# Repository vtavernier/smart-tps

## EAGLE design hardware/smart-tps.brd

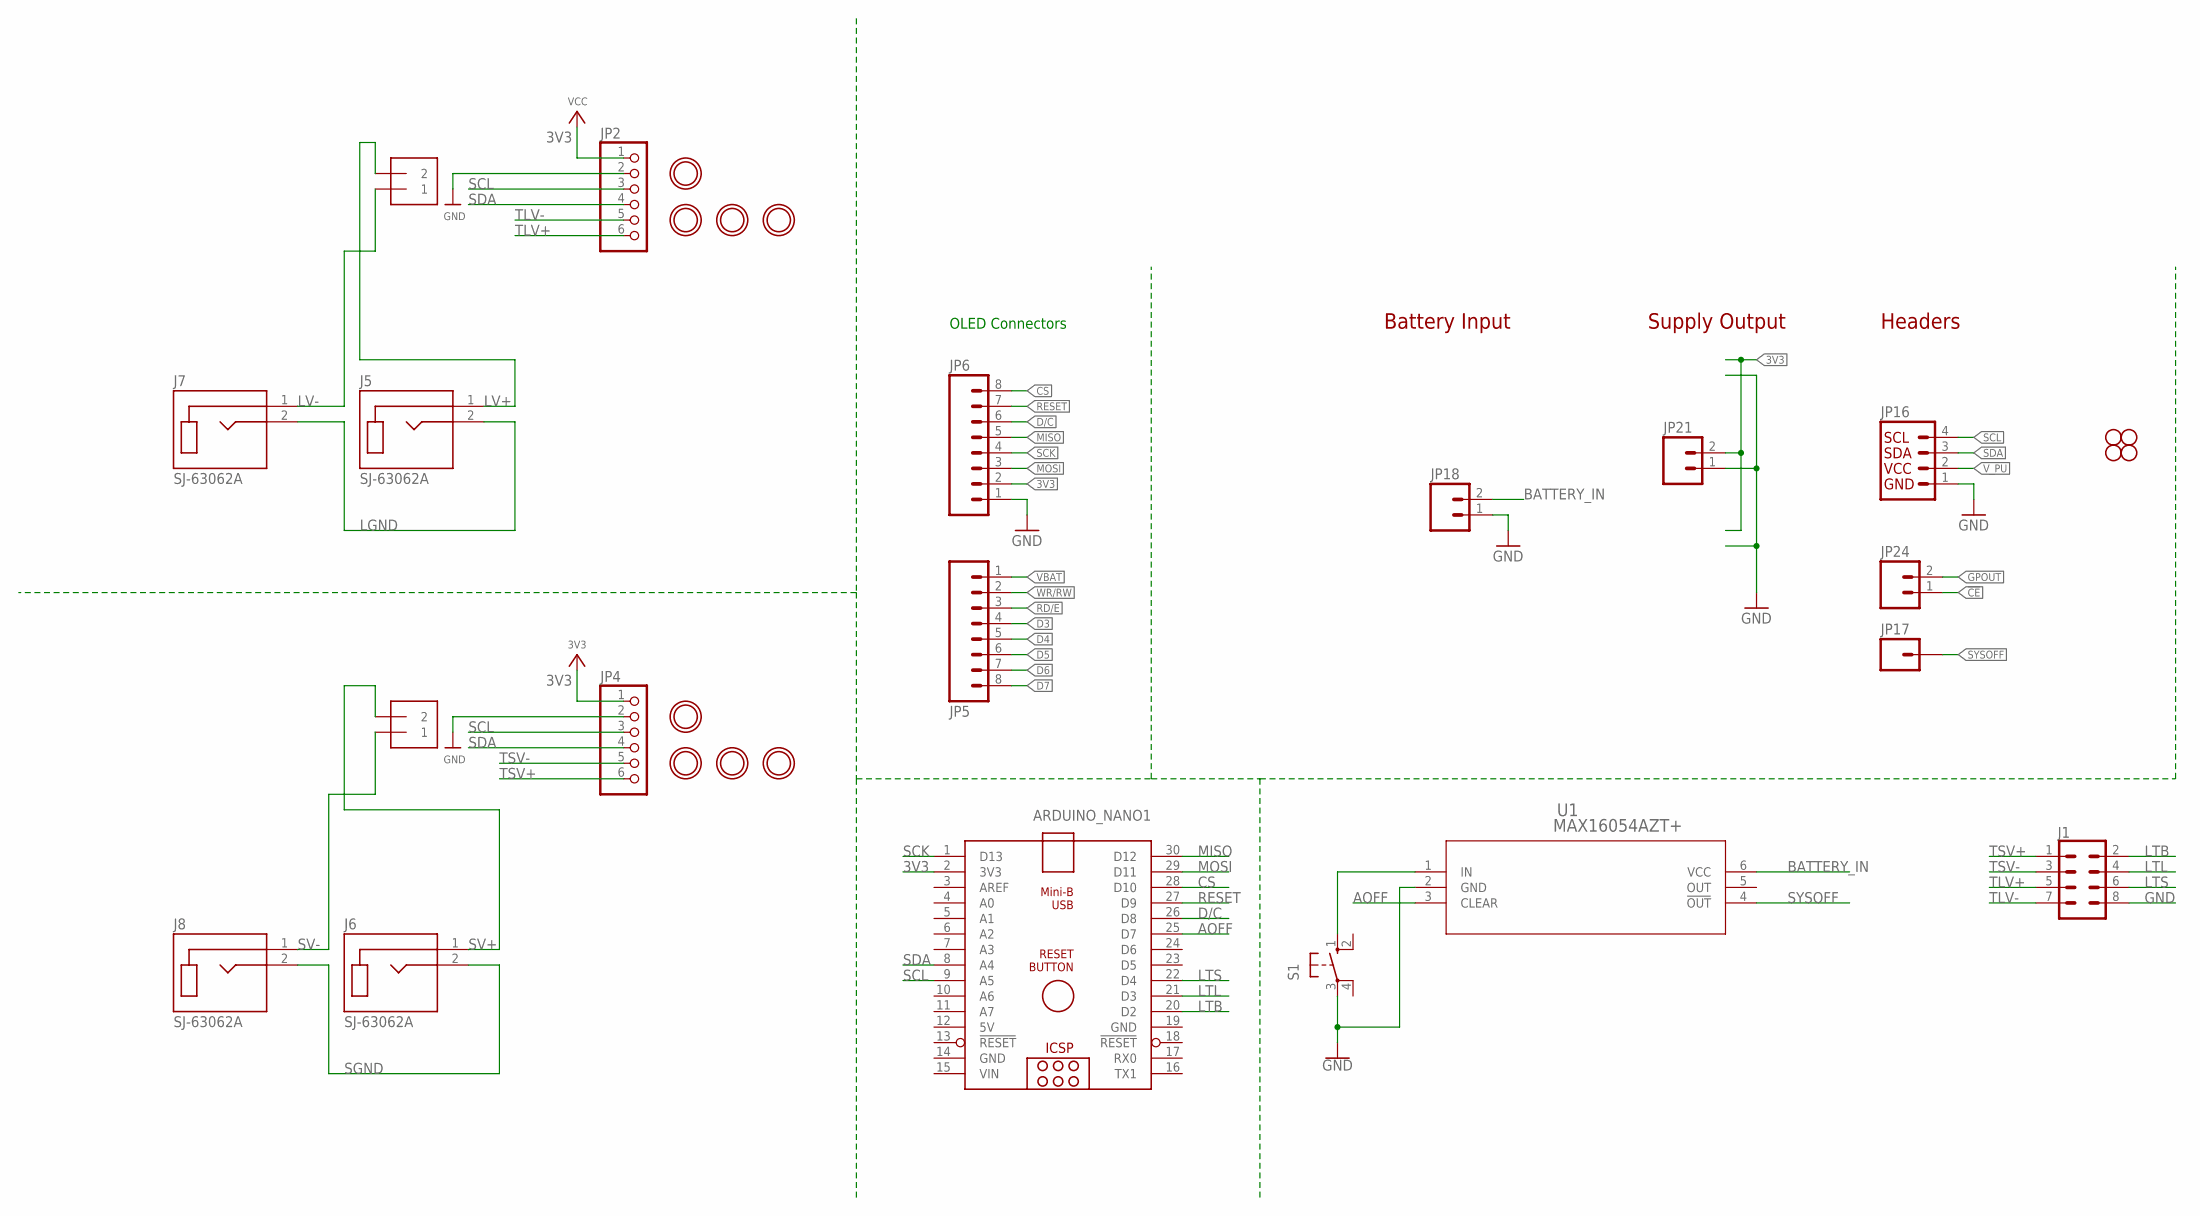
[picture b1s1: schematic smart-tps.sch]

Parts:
ARDUINO_NANO1: ARDUINO_NANO
J1: CONN_04X2; 2X4
J2, J4: TERMBLOCK_1X2-3.5MM; 1X2-3.5MM
J5, J6, J7, J8: SJ-63062A; CUI_SJ-63062A
JP2, JP4: HEADER-1X670MIL; 1X06_ROUND_70
JP5, JP6: M08; 1X08_PIN1_NO_SILK
JP16: I2C_STANDARD_NO_SILK; 1X04_NO_SILK
JP17: M01PTH_NO_SILK_YES_STOP; 1X01_NO_SILK
JP18, JP21, JP24: M021X02_NO_SILK; 1X02_NO_SILK@1
S1: 10-XX; B3F-10XX
STANDOFF5, STANDOFF6, STANDOFF7, STANDOFF8: STAND-OFF
U1: MAX16054AZT+; 21-0114C_MXM
U$18, U$19, U$20, U$21, U$40, U$41, U$42, U$43: MOUNTINGHOLE2.5; MOUNTINGHOLE_2.5_PLATED

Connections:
3V3: ARDUINO_NANO1.2 (3V3), JP2.1, JP4.1, JP6.2, JP21.2
5V: ARDUINO_NANO1.12 (5V)
!CE!: JP24.1
AOFF: ARDUINO_NANO1.25 (D7), U1.3 (CLEAR)
BATTERY_IN: JP18.2, U1.6 (VCC)
CS: ARDUINO_NANO1.28 (D10), JP6.8
D3: JP5.4
D4: JP5.5
D5: JP5.6
D6: JP5.7
D7: JP5.8
D/C: ARDUINO_NANO1.26 (D8), JP6.6
GND: ARDUINO_NANO1.14 (GND), ARDUINO_NANO1.19 (GND), J1.8, JP2.2, JP4.2, JP6.1, JP16.1, JP18.1, JP21.1, S1.3, U1.2 (GND)
GPOUT: JP24.2
LGND: J5.2 (TIP), J7.2 (TIP)
LTB: ARDUINO_NANO1.20 (D2), J1.2
LTL: ARDUINO_NANO1.21 (D3), J1.4
LTS: ARDUINO_NANO1.22 (D4), J1.6
LV+: J2.2, J5.1 (SLEEVE)
LV-: J2.1, J7.1 (SLEEVE)
MISO: ARDUINO_NANO1.30 (D12), JP6.5
MOSI: ARDUINO_NANO1.29 (D11), JP6.3
unnamed: S1.1 (S), U1.1 (IN)
RD/E: JP5.3
RESET: ARDUINO_NANO1.27 (D9), JP6.7
SCK: ARDUINO_NANO1.1 (D13), JP6.4
SCL: ARDUINO_NANO1.9 (A5), JP2.3, JP4.3, JP16.4
SDA: ARDUINO_NANO1.8 (A4), JP2.4, JP4.4, JP16.3
SGND: J6.2 (TIP), J8.2 (TIP)
SV+: J4.2, J6.1 (SLEEVE)
SV-: J4.1, J8.1 (SLEEVE)
SYSOFF: JP17.1, U1.4 (!OUT)
TLV+: J1.5, JP2.6
TLV-: J1.7, JP2.5
TSV+: J1.1, JP4.6
TSV-: J1.3, JP4.5
VBAT: JP5.1
VIN: ARDUINO_NANO1.15 (VIN)
V_PU: JP16.2
WR/RW: JP5.2

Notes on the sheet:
Battery Input
Supply Output
Headers
OLED Connectors

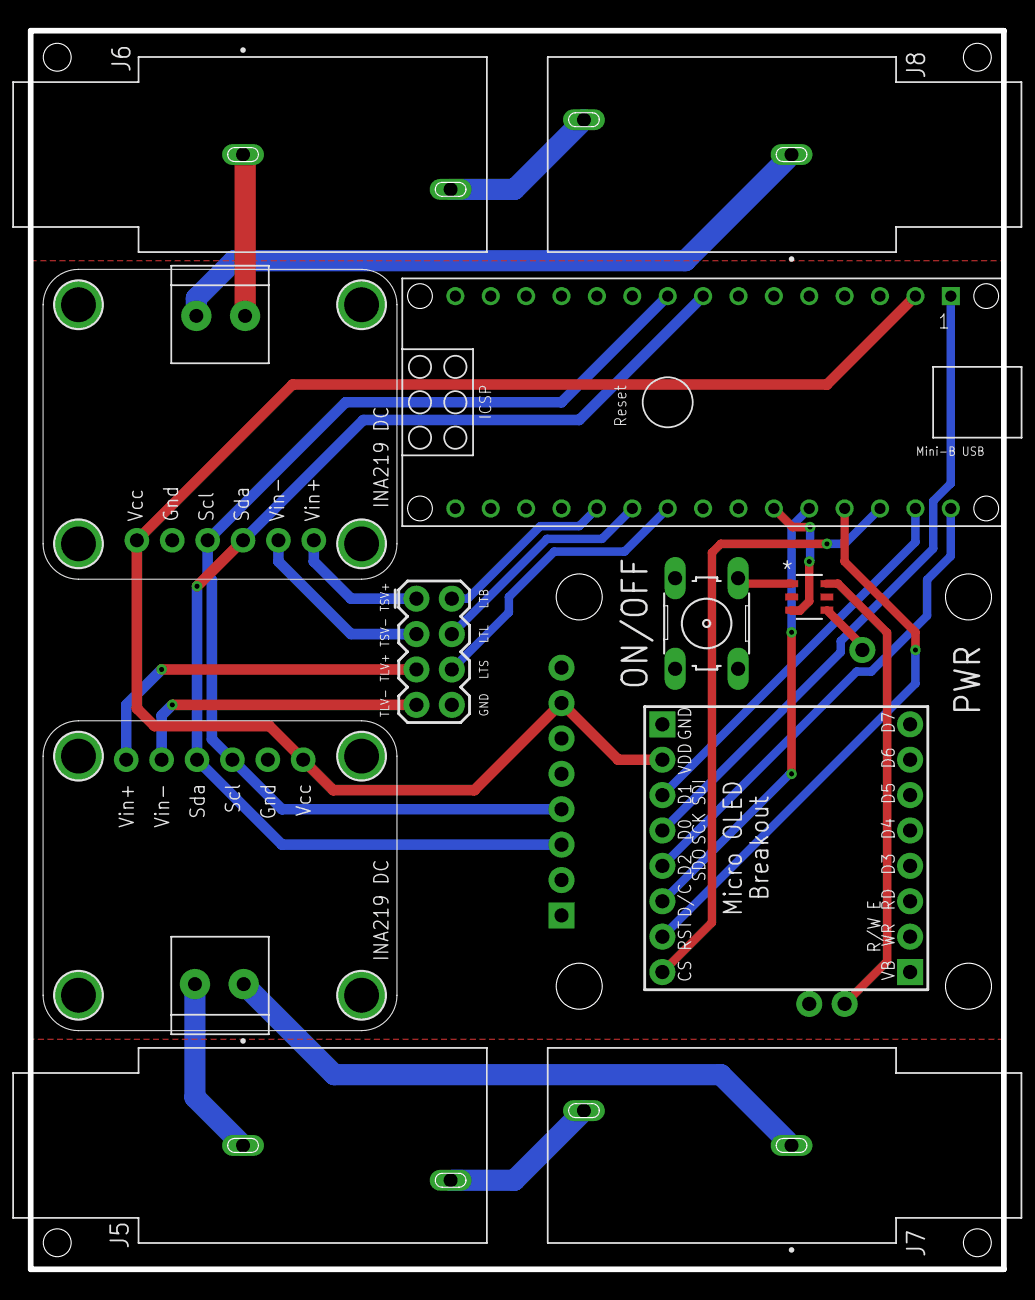
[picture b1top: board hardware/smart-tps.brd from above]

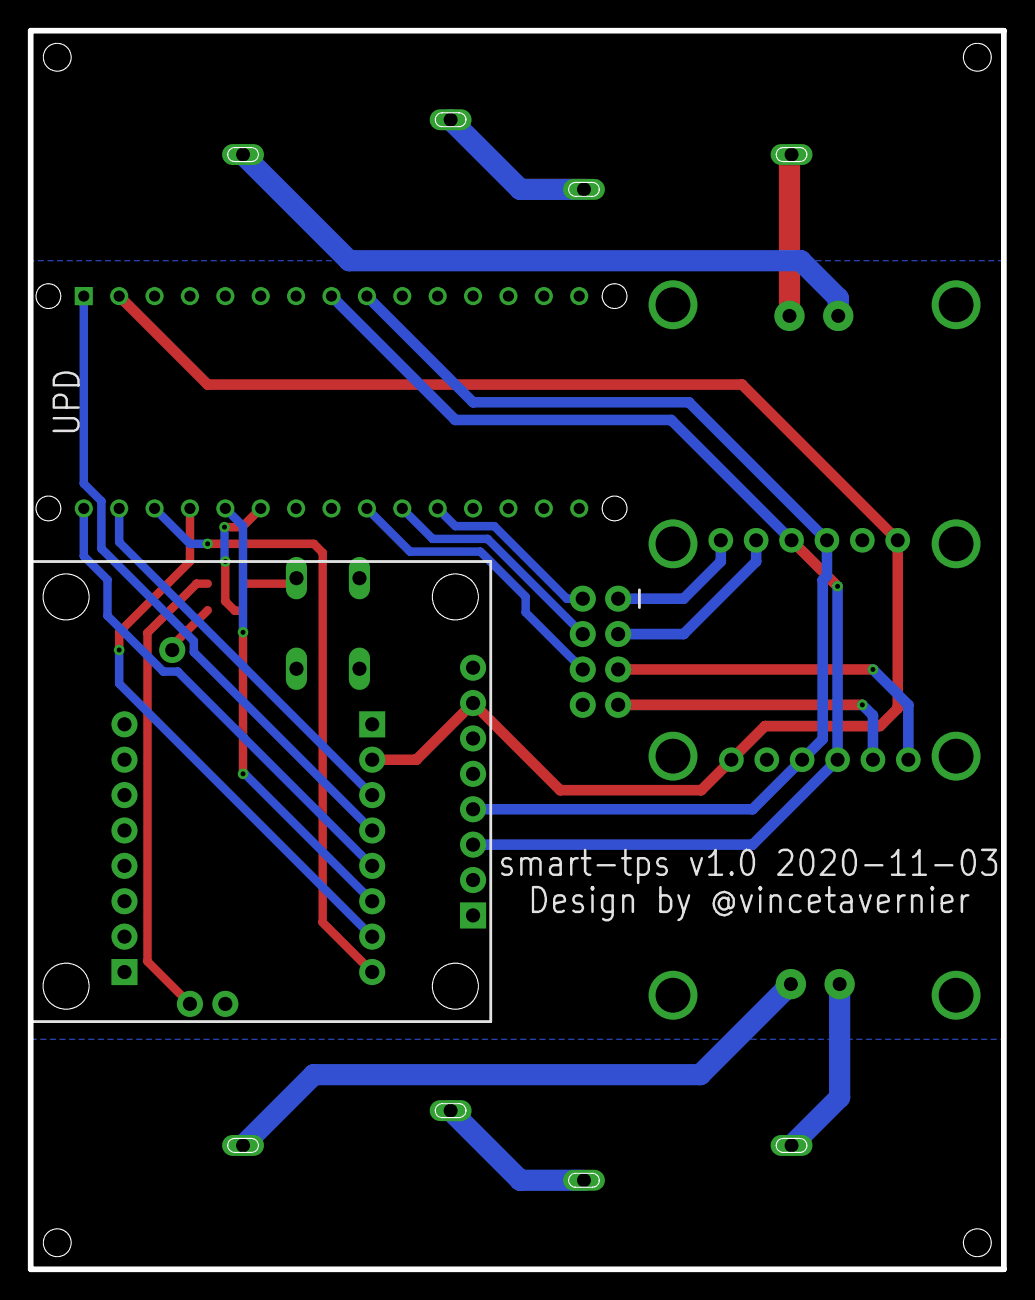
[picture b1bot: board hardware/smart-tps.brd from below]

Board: 2 copper layers, 69.8 x 88.9 mm, 31 parts (9 on the bottom side), 27 nets.

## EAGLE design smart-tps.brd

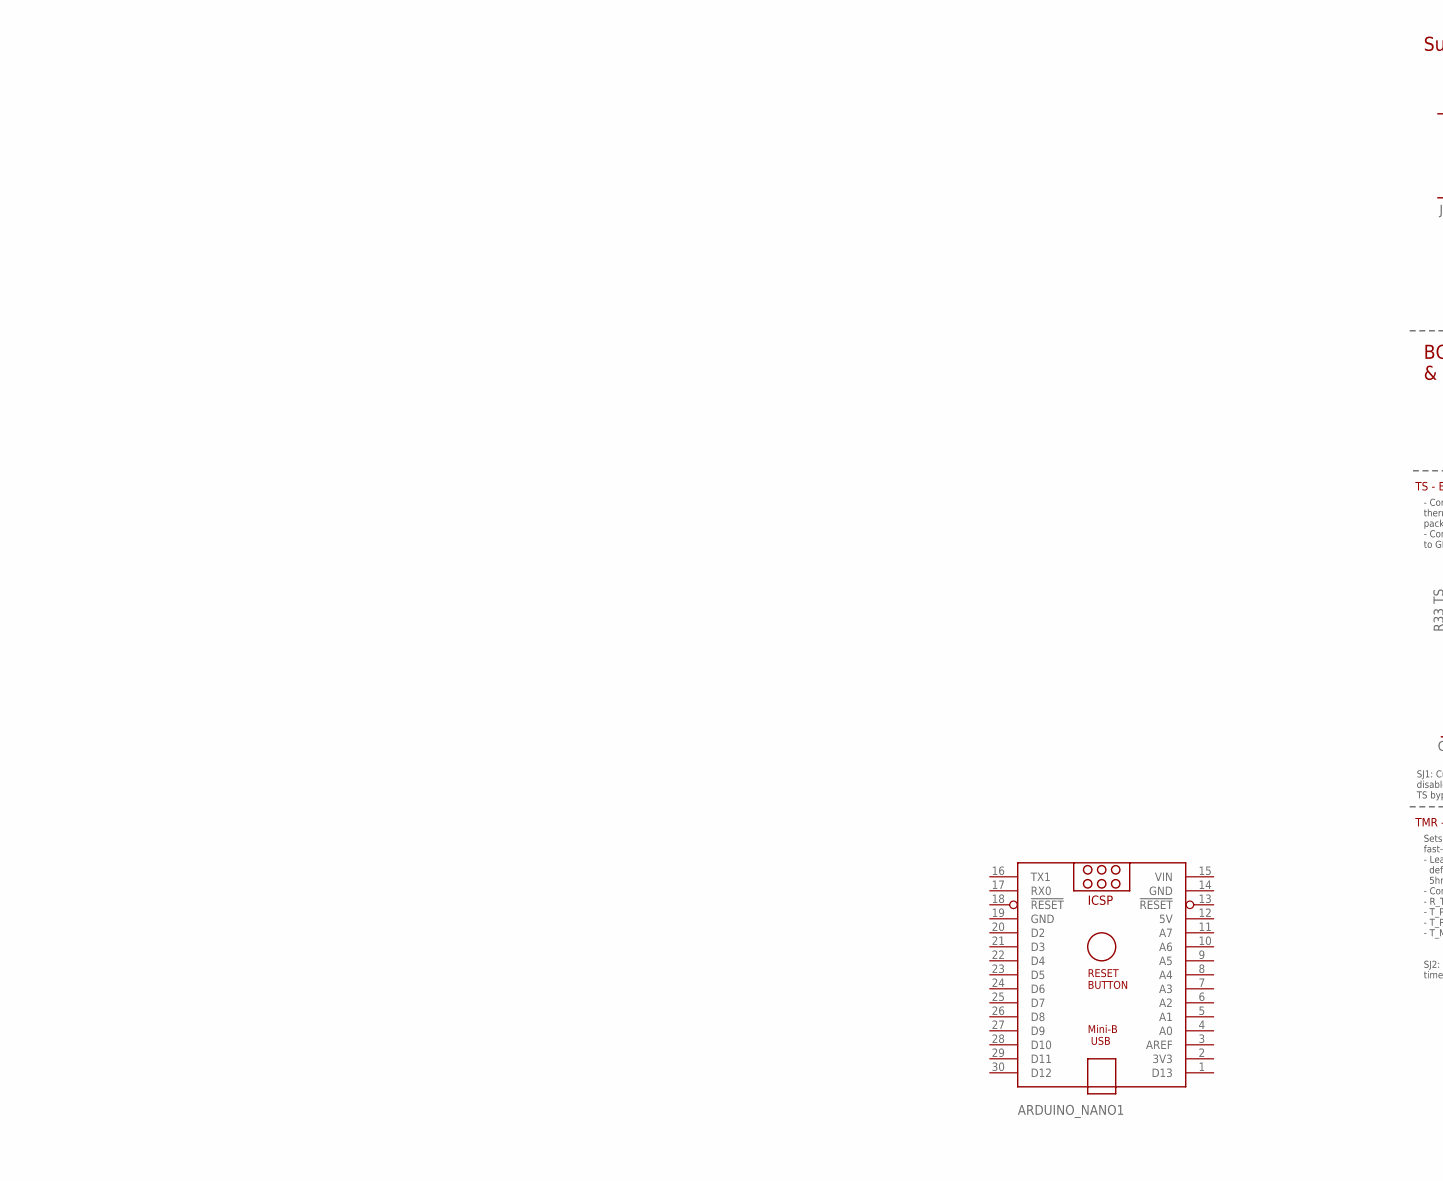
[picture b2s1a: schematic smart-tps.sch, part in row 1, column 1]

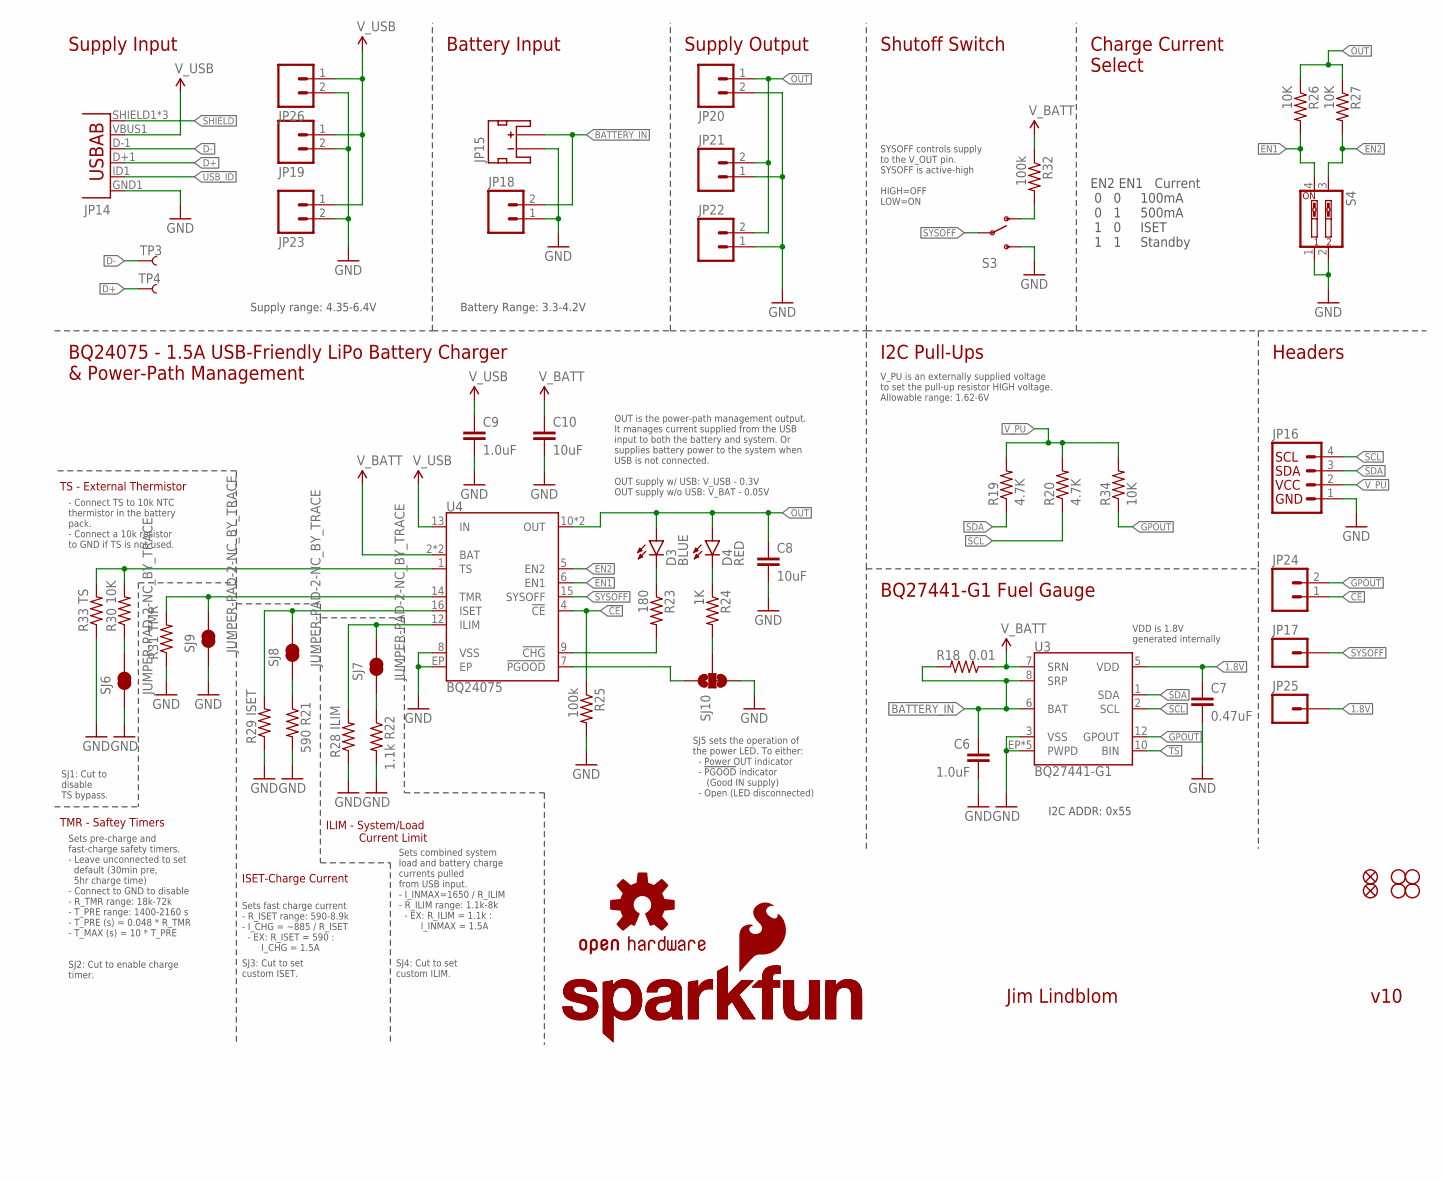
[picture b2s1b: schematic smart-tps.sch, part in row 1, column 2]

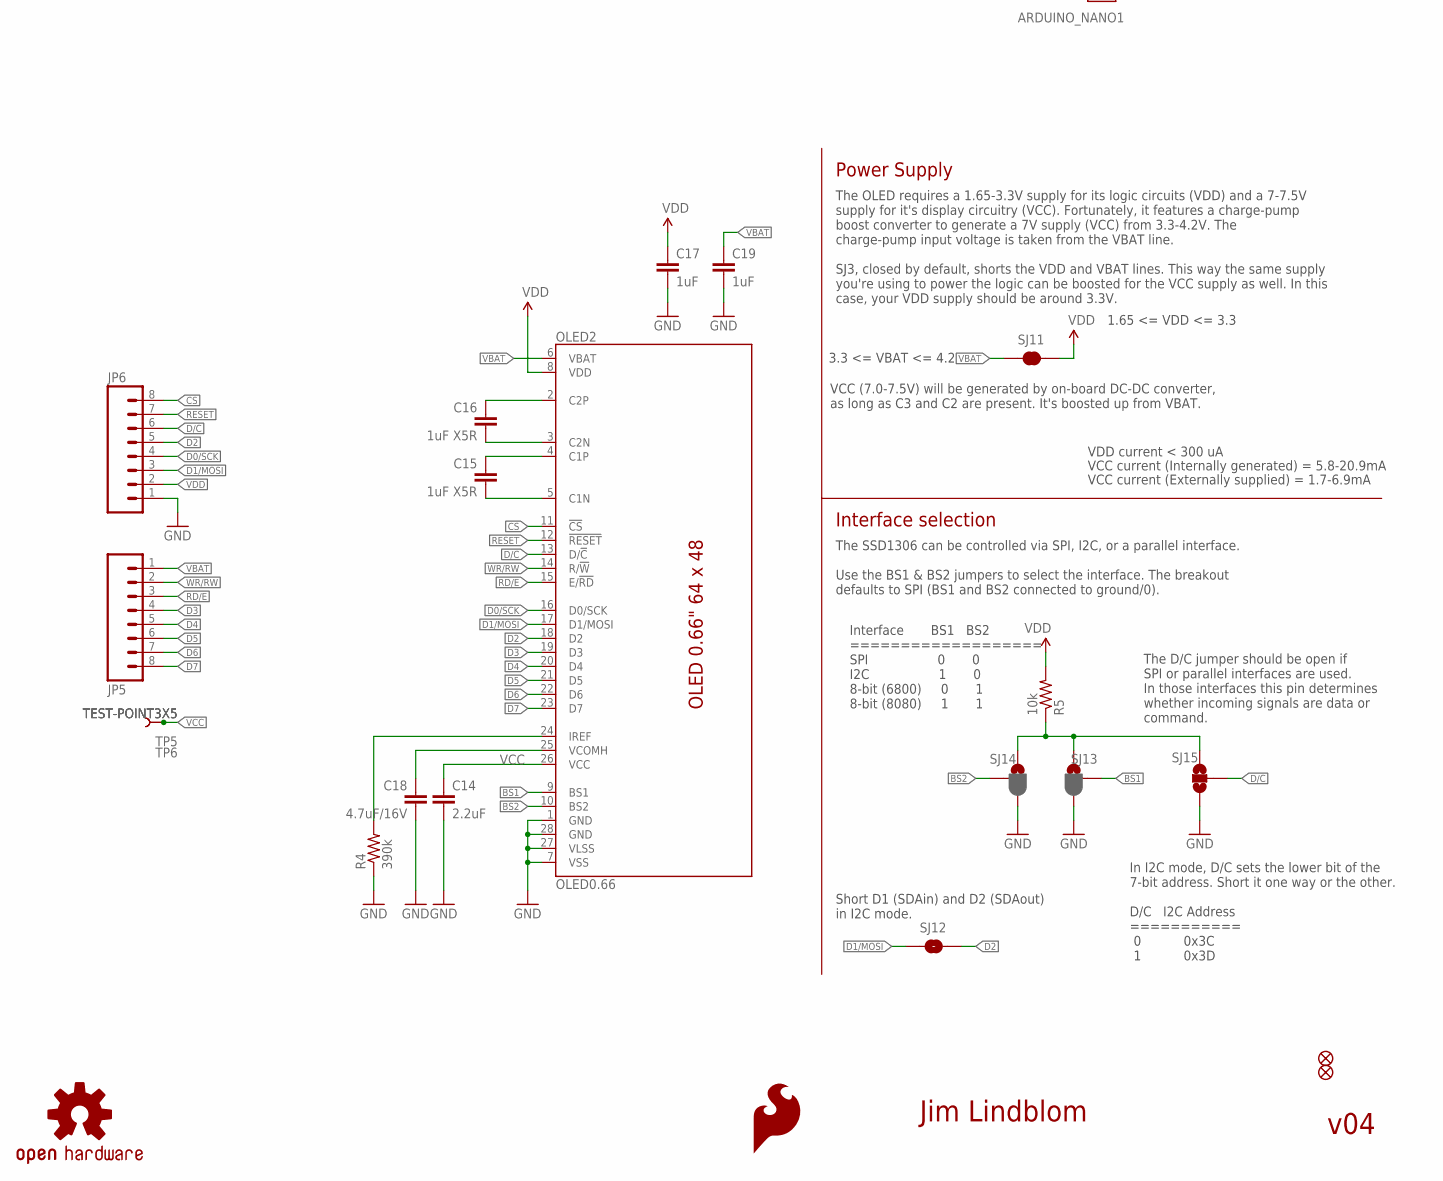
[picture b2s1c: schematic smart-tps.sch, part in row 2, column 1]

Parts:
ARDUINO_NANO1: ARDUINO_NANO
C6: 1.0uF; 0603-CAP
C7: 0.47uF; 0603-CAP
C8, C10: 10uF; 0805-CAP
C9: 1.0uF; 1206-CAP
C14: 2.2uF; 0805
C15, C16: 1uF X5R; 0805
C17, C19: 1uF; 0603-CAP
C18: 4.7uF/16V; 1206
D3: BLUE; LED-0603
D4: RED; LED-0603
FID3, FID4, FID5, FID6: FIDUCIAL1X2; FIDUCIAL-1X2
JP5, JP6: M08; 1X08_PIN1_NO_SILK
JP14: USB-ABCONN-11794; USB-AB-MICRO-SMD_V03
JP15: JST_2MM_MALE; JST-2-SMD
JP16: I2C_STANDARD_NO_SILK; 1X04_NO_SILK
JP17, JP25: M01PTH_NO_SILK_YES_STOP; 1X01_NO_SILK
JP18, JP21, JP23, JP24, JP26: M021X02_NO_SILK; 1X02_NO_SILK@1
JP19, JP20: M023.5MM-NO_SILK; SCREWTERMINAL-3.5MM-2-NS@1
JP22: M02-JST-2-PTH-NO_SILK; JST-2-PTH-NS@1
LOGO4: SFE_LOGO_NAME.1_INCH; SFE_LOGO_NAME_.1
LOGO5, LOGO11: OSHW-LOGOS; OSHW-LOGO-S
LOGO6: SFE_LOGO_NAME_FLAME.1_INCH; SFE_LOGO_NAME_FLAME_.1
LOGO10: SFE_LOGO_FLAME.1_INCH; SFE_LOGO_FLAME_.1
OLED2: OLED0.66; OLED-0.66-64X48
R4: 390k; 0603-RES
R5: 10k; 0603-RES
R18: 0.01; 1206
R19, R20: 4.7K; 0603-RES
R21: 590; 0603-RES
R22: 1.1k; 0603-RES
R23: 180; 0603-RES
R24: 1K; 0603-RES
R25, R32: 100k; 0603-RES
R26, R27, R30, R34: 10K; 0603-RES
R28: ILIM; 1/6W-RES
R29: ISET; 1/6W-RES
R31: TMR; 1/6W-RES
R33: TS; 1/6W-RES
S3: SWITCH-SPDT-SMD-A; SWITCH-SPST-SMD-A
S4: SW_DIP-2-SMT-HALFSIZE; DIPSWITCH-02-50MIL
SJ6, SJ7, SJ8, SJ9: JUMPER-PAD-2-NC_BY_TRACE; PAD-JUMPER-2-NC_BY_TRACE_YES_SILK
SJ10: JUMPER-PAD-3-2OF3_NC_BY_TRACE_SMALL; PAD-JUMPER-3-2OF3_NC_BY_TRACE_YES_SILK_FULL_BOX
SJ11: JUMPER-PAD-2-NC_BY_TRACENO_SILK; PAD-JUMPER-2-NC_BY_TRACE_NO_SILK
SJ12: JUMPER-PAD-2-NOYES_SILK; PAD-JUMPER-2-NO_YES_SILK
SJ13: BS1; PAD-JUMPER-3-2OF3_NC_BY_PASTE_YES_SILK_FULL_BOX
SJ14: BS2; PAD-JUMPER-3-2OF3_NC_BY_PASTE_YES_SILK_FULL_BOX
SJ15: JUMPER-PAD-3-NOTIGHT; PAD-JUMPER-3-NO-TIGHT
STANDOFF5, STANDOFF6, STANDOFF7, STANDOFF8: STAND-OFF
TP3, TP4: TEST-POINT3X4; PAD.03X.04
TP5, TP6: TEST-POINT3X5; PAD.03X.05
U3: BQ27441-G1; PDSO-N12
U4: BQ24075; PVQFN-N16

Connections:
1.8V: C7.1, JP25.1, U3.5 (VDD)
5V: ARDUINO_NANO1.12 (5V)
!CE!: JP24.1, R25.1, U4.4 (!CE!)
!CHG!1: R23.2, U4.9 (!CHG!)
!PGOOD!1: SJ10.1, U4.7 (!PGOOD!)
BATTERY_IN: C6.1, JP15.2 (+), JP18.2, R18.2, U3.6 (BAT), U3.8 (SRP)
BS1: OLED2.9 (BS1), SJ13.2
BS2: OLED2.10 (BS2), SJ14.2
C1N1: C15.2, OLED2.5 (C1N)
C1P1: C15.1, OLED2.4 (C1P)
C2N1: C16.2, OLED2.3 (C2N)
C2P1: C16.1, OLED2.2 (C2P)
CS: JP6.8, OLED2.11 (!CS!)
D0/SCK: JP6.4, OLED2.16 (D0/SCK)
D1/MOSI: JP6.3, OLED2.17 (D1/MOSI), SJ12.1
D2: JP6.5, OLED2.18 (D2), SJ12.2
D3: JP5.4, OLED2.19 (D3)
D4: JP5.5, OLED2.20 (D4)
D5: JP5.6, OLED2.21 (D5)
D6: JP5.7, OLED2.22 (D6)
D7: JP5.8, OLED2.23 (D7)
D+: JP14.D+1 (D+), TP4.P$1
D-: JP14.D-1 (D-), TP3.P$1
D/C: JP6.6, OLED2.13 (D/!C!), SJ15.2
EN1: R26.2, S4.4, U4.6 (EN1)
EN2: R27.2, S4.3, U4.5 (EN2)
GND: ARDUINO_NANO1.14 (GND), ARDUINO_NANO1.19 (GND), C6.2, C7.2, C8.2, C9.2, C10.2, C14.2, C17.2, C18.2, C19.2, JP6.1, JP14.GND1 (GND), JP15.1 (-), JP16.1, JP18.1, JP19.2, JP20.2, JP21.1, JP22.1, JP23.2, JP26.2, OLED2.1 (GND), OLED2.7 (VSS), OLED2.27 (VLSS), OLED2.28 (GND), R4.1, R21.2, R22.2, R25.2, R28.1, R29.1, R31.1, R33.1, S3.3 (S), S4.1, S4.2, SJ6.1, SJ9.1, SJ10.3, SJ13.3, SJ14.3, SJ15.3, U3.3 (VSS), U3.EP (PWPD), U3.EP1 (PWPD), U3.EP2 (PWPD), U3.EP3 (PWPD), U3.EP4 (PWPD), U4.8 (VSS), U4.EP
GPOUT: JP24.2, R34.1, U3.12 (GPOUT)
ILIM1: R28.2, SJ7.2, U4.12 (ILIM)
IREF1: OLED2.24 (IREF), R4.2
ISET1: R29.2, SJ8.2, U4.16 (ISET)
unnamed: D3.C, R23.1
unnamed: D4.C, R24.1
unnamed: R32.2, S3.1 (O)
unnamed: R30.1, SJ6.2
unnamed: R22.1, SJ7.1
unnamed: R21.1, SJ8.1
unnamed: R24.2, SJ10.2
OUT: C8.1, D3.A, D4.A, JP20.1, JP21.2, JP22.2, R26.1, R27.1, U4.10 (OUT), U4.11 (OUT)
RD/E: JP5.3, OLED2.15 (E/!RD!)
RESET: JP6.7, OLED2.12 (!RESET!)
SCL: JP16.4, R20.1, U3.2 (SCL)
SDA: JP16.3, R19.1, U3.1 (SDA)
SHIELD: JP14.SHIELD1 (SHIELD), JP14.SHIELD2 (SHIELD), JP14.SHIELD3 (SHIELD)
SYSOFF: JP17.1, S3.2, U4.15 (SYSOFF)
TMR1: R31.2, SJ9.2, U4.14 (TMR)
TS: R30.2, R33.2, U3.10 (BIN), U4.1 (TS)
USB_ID: JP14.ID1 (USBID)
VBAT: C19.1, JP5.1, OLED2.6 (VBAT), SJ11.1
VCC: C14.1, OLED2.26 (VCC), TP5.P$1, TP6.P$1
VCOMH1: C18.1, OLED2.25 (VCOMH)
VDD: C17.1, JP6.2, OLED2.8 (VDD), R5.2, SJ11.2
VDD_PU1: R5.1, SJ13.1, SJ14.1, SJ15.1
VIN: ARDUINO_NANO1.15 (VIN)
V_BATT: C10.1, R18.1, R32.1, U3.7 (SRN), U4.2 (BAT), U4.3 (BAT)
V_PU: JP16.2, R19.2, R20.2, R34.2
V_USB: C9.1, JP14.VBUS1 (VBUS), JP19.1, JP23.1, JP26.1, U4.13 (IN)
WR/RW: JP5.2, OLED2.14 (R/!W!)

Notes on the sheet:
EN2 EN1 Current 0 0 100mA 0 1 500mA 1 0 ISET 1 1 Standby
Sets fast charge current - R_ISET range: 590-8.9k - I_CHG = ~885 / R_ISET - EX: R_ISET = 590 : I_CHG = 1.5A
Sets combined system load and battery charge currents pulled from USB input. - I_INMAX=1650 / R_ILIM - R_ILIM range: 1.1k-8k - EX: R_ILIM = 1.1k : I_INMAX = 1.5A
Supply Input
Battery Input
Supply Output
Shutoff Switch
Charge Current Select
BQ24075 - 1.5A USB-Friendly LiPo Battery Charger & Power-Path Management
I2C Pull-Ups
BQ27441-G1 Fuel Gauge
Headers
Jim Lindblom
v10
SYSOFF controls supply to the V_OUT pin. SYSOFF is active-high HIGH=OFF LOW=ON
SJ1: Cut to disable TS bypass.
SJ3: Cut to set custom ISET.
SJ4: Cut to set custom ILIM.
ILIM - System/Load Current Limit
ISET-Charge Current
TMR - Saftey Timers
Sets pre-charge and fast-charge safety timers. - Leave unconnected to set default (30min pre, 5hr charge time) - Connect to GND to disable - R_TMR range: 18k-72k - T_PRE range: 1400-2160 s - T_PRE (s) = 0.048 * R_TMR - T_MAX (s) = 10 * T_PRE
SJ2: Cut to enable charge timer.
TS - External Thermistor
- Connect TS to 10k NTC thermistor in the battery pack. - Connect a 10k resistor to GND if TS is not used.
V_PU is an externally supplied voltage to set the pull-up resistor HIGH voltage. Allowable range: 1.62-6V
Supply range: 4.35-6.4V
VDD is 1.8V generated internally
OUT is the power-path management output. It manages current supplied from the USB input to both the battery and system. Or supplies battery power to the system when USB is not connected. OUT supply w/ USB: V_USB - 0.3V OUT supply w/o USB: V_BAT - 0.05V
I2C ADDR: 0x55
SJ5 sets the operation of the power LED. To either: - Power OUT indicator - !PGOOD! indicator (Good IN supply) - Open (LED disconnected)
Battery Range: 3.3-4.2V
v04
1.65 <= VDD <= 3.3
VDD current < 300 uA
VCC current (Internally generated) = 5.8-20.9mA
VCC current (Externally supplied) = 1.7-6.9mA
Interface BS1 BS2 =================== SPI 0 0 I2C 1 0 8-bit (6800) 0 1 8-bit (8080) 1 1
VCC (7.0-7.5V) will be generated by on-board DC-DC converter, as long as C3 and C2 are present. It's boosted up from VBAT.
3.3 <= VBAT <= 4.2

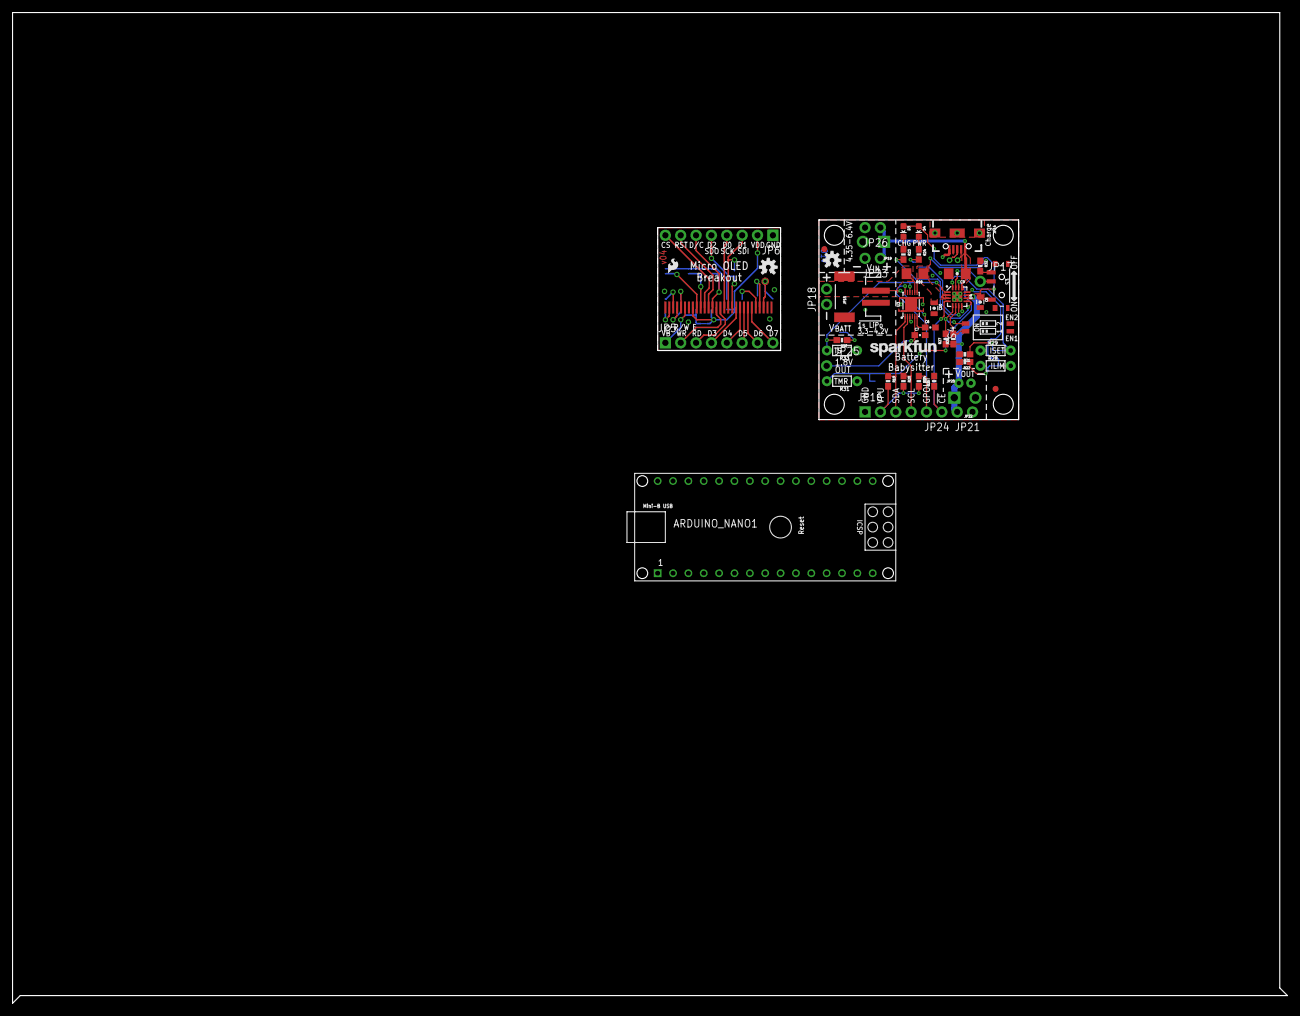
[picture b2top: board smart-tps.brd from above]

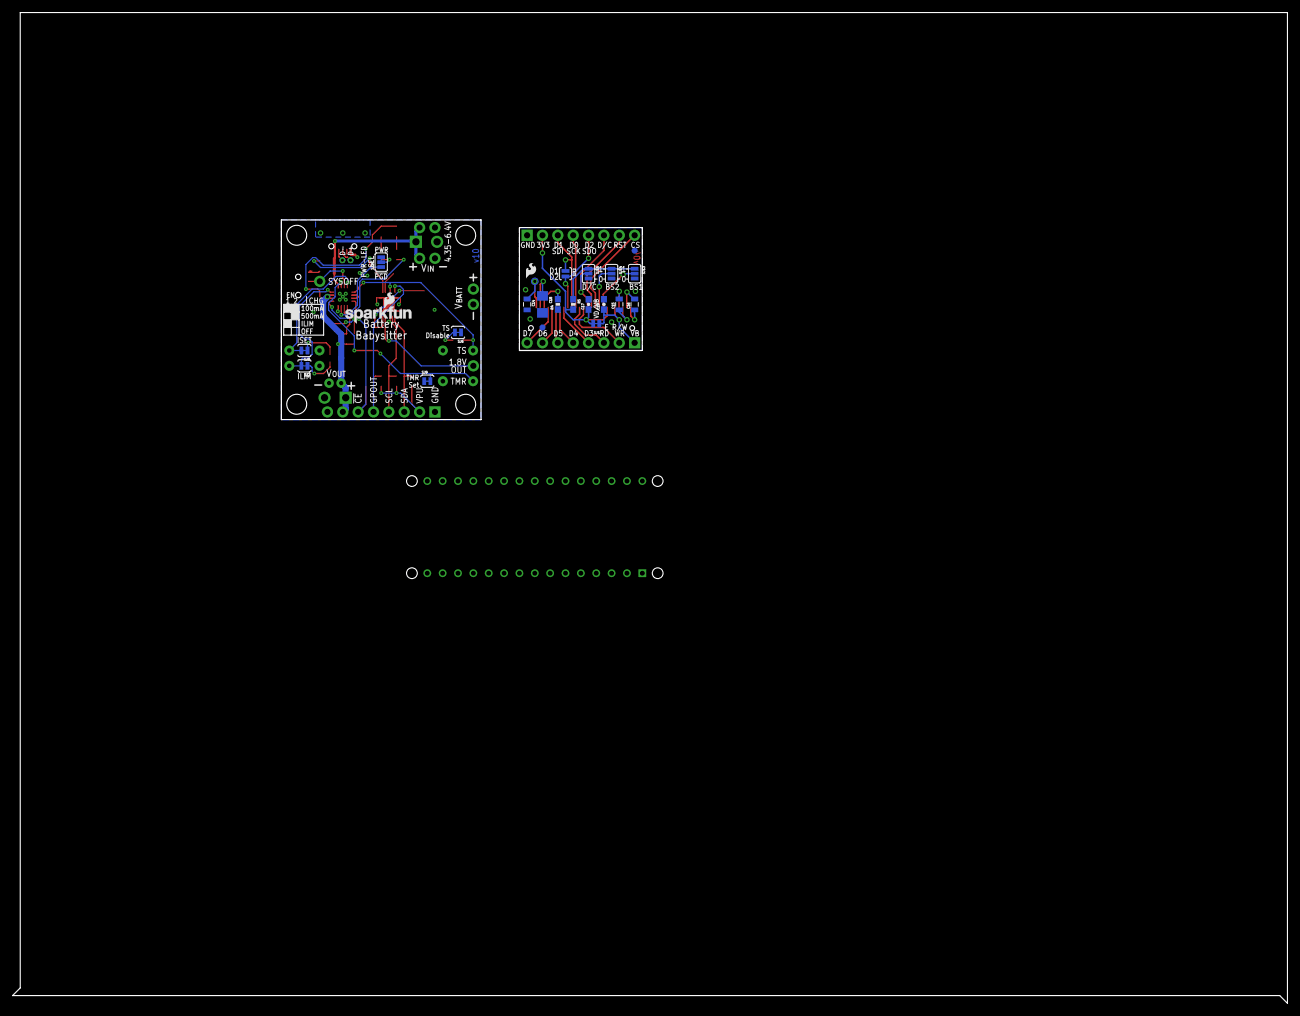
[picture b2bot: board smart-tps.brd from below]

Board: 2 copper layers, 210.8 x 163.8 mm, 81 parts (25 on the bottom side), 55 nets.

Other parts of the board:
LOGO12: SFE_LOGO_FLAME.1_INCH; SFE_LOGO_FLAME_.1

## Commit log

2020-12-05 Introduce Tps class
2020-12-05 Update schematic
2020-12-05 Reformat code
2020-12-05 Add current test and basic OLED display code
2020-12-05 Commit final version of PCB
2020-12-05 Disable extra Pwm because of mbed limitation
2020-12-05 Fix duty cycle computation
2020-12-05 First somewhat working version
2020-12-05 Add NrfPwmPort class and use it for RGB LED
2020-12-05 Reorganize repository
2020-12-06 Switch to Adafruit OLED library
2020-12-06 Add native test target
2020-12-06 Add Rust crate for implementing extra functionality
2020-12-06 Add TPS_VERSION macro
2020-12-06 Add GUI abstraction layer
2020-12-06 Abstract all hardware components
2020-12-06 Abstract Arduino platform
2020-12-06 Use ncurses UI for native simulator
2020-12-06 Fix GUI state operator==
2020-12-06 Actually generate PWM signal on native
2020-12-07 Add battery level icons
2020-12-07 Only show seconds on screen
2020-12-07 Extract stats computation to its own class
2020-12-07 Extract LoadType into its own header
2020-12-08 Disable power led
2020-12-08 Prepare main state machine implementation, better load simulator code
2020-12-08 Implement main state machine
2020-12-16 Add current sensor dump support
2020-12-16 Remove offset in native load simulator
2020-12-16 Update thresholds
2020-12-16 Update notebooks
2020-12-16 On native, load values from CSV file
2020-12-16 Compute mean period using a trimmed mean
2020-12-16 Limit measure rate on native
2020-12-16 Slight smoothing of output values
2020-12-16 Fix display issues
2020-12-22 Compute stats using a frequency histogram

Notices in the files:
parts and their libraries:
SparkFun-Connectors: Licensing: Creative Commons ShareAlike 4.0 International - https://creativecommons.org/licenses/by-sa/4.0
